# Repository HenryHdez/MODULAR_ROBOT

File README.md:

# **MODULAR ROBOT **
# **PROJECT "PCB"**
Here are all the PCB's for manufacturing the EMERGE modular robot.
# **PROJECT "Optimization_Algorithms.rar" CONTENT**
The content of this project is divided into three sections:
* The first "Module" project must be programmed in all modules of the robotic platform.
* The Second Project "Xbee_Snifer_Teraterm" must be programmed in the accessory card that has an Xbee module only (previously configured) and to perform the data registration you can use the project "Capture_Interface.rar" which is designed in MATLAB and simply begins its registration by pressing the Start button and turn on the robot.
To configure the Xbee module you can follow the following link;
http://xbee.cl/xbee-serie-2-configuracion/
* Finally, there are optimization algorithms, of which you must choose one and program it in the accessory that has the ultrasound sensor only.
# **PROJECT "Robot_Test.rar" CONTENT**
This project is used to test the different peripherals of the robot.
## Test_LED	
This code activates (Frecuency=10Hz) LED lights on each side.
## Test_All_Sensor	
The initialization routine is in charge of turning on the LED located next to each sensor, it will do it 5 times if there is communication with it, otherwise it will only do it once.
Once initialize each sensor, if one of them is obstructed turn on the LED that is next to it.
## Test_Motor	
This program turns on the motor led once it communicates with it, moves it from right to left and vice versa at intervals of 5 seconds.
## Test_Sensor_F1	
All LEDs turn on and off, if there is communication with the face sensor 1.
## Test_Sensor_F2	
All LEDs turn on and off, if there is communication with the face sensor 2.
## Test_Sensor_F3	
All LEDs turn on and off, if there is communication with the face sensor 3.
## Test_Sensor_F4	
All LEDs turn on and off, if there is communication with the face sensor 4.
## Test_CAN_Module_1
Each module sends and receives a data, if the data is accepted, turn on the led of face 2 in each module, otherwise it will not turn on.
## Test_CAN_Module_2	
CAN_Psoc_kit	
Show the information on the CAN bus on an LCD display.

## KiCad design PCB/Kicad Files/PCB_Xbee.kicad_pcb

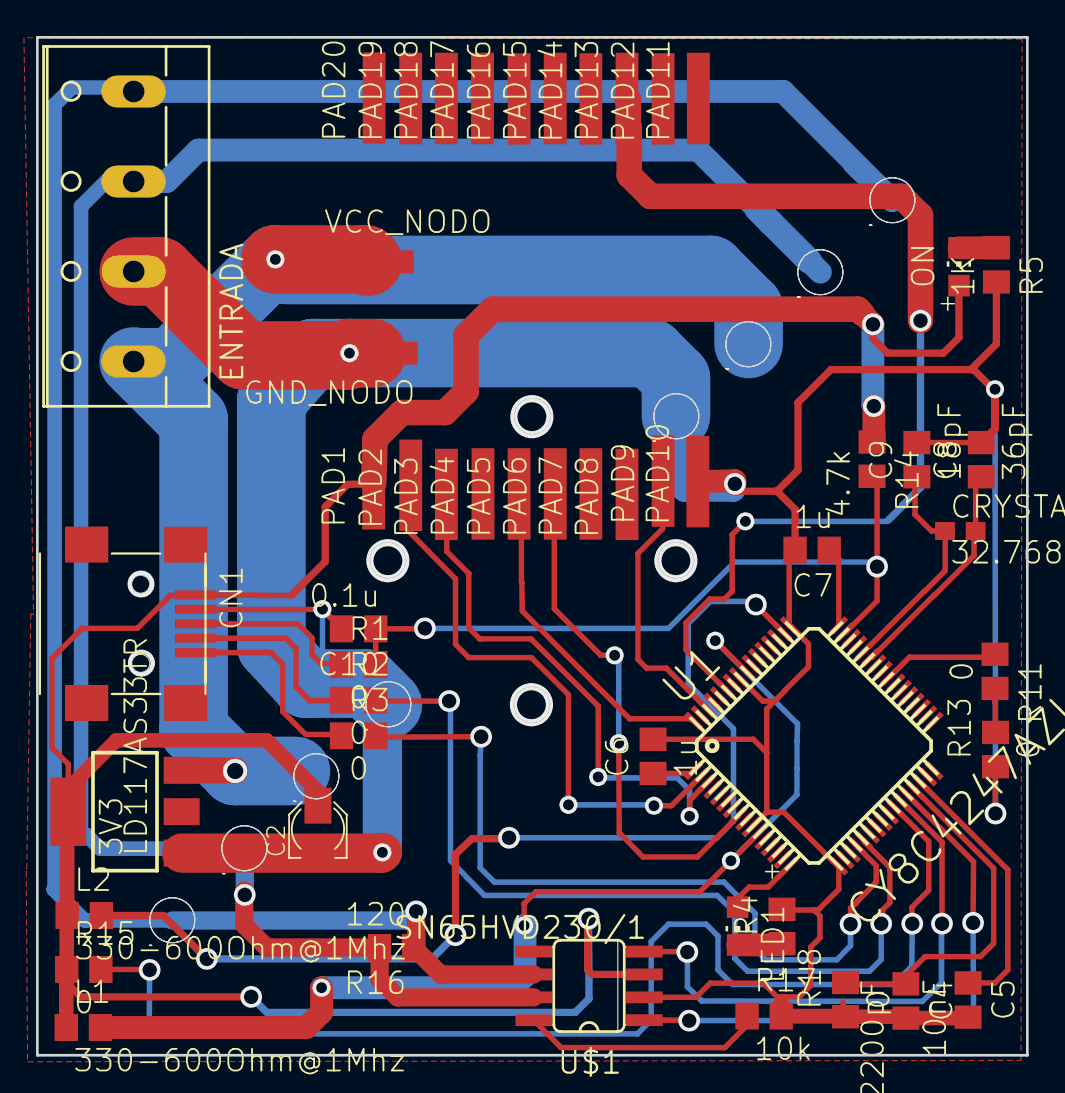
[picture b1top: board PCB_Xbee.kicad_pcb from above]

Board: 2 copper layers, 55.0 x 56.5 mm, 60 parts (0 on the bottom side), 34 nets.

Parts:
3V3: LD117AS33TR; SOT223
C2: PANASONIC_A
C4: 2200pF; C0805
C5: 10nF; C0805
C6, C7: 1u; C0805
C8: 36pF; C0805
C9: 18pF; C0805
C10: 0.1u; C0805
CANH_1_C1, CANH_1_C2: TPB2,54; B2,54
CANL_1_C1, CANL_1_C2: TPB2,54; B2,54
CN1: USB-MINIB
CRYSTAL: 32.768kHz; C0603
ENTRADA: W237-4
GND_1_C1, GND_1_C2: TPB2,54; B2,54
GND_NODO: SMD2,54-5,08
L1, L2: 330-600Ohm@1Mhz; R0805
LED1: CHIP-LED0805
ON: CHIP-LED0805
PAD1, PAD2, PAD3, PAD4, PAD5, PAD6, PAD7, PAD8, PAD9, PAD10, PAD11, PAD12, PAD13, PAD14, PAD15, PAD16, PAD17, PAD18, PAD19, PAD20: SMD2,54-5,08
R1, R2, R3, R11, R13, R15, R18: 0; R0805
R4: R0805
R5: 1K; R0805
R14: 4.7k; R0805
R16: 120; R0805
R17: 10k; R0805
U1: CY8C4247AZI-M485; TQFP64-10X10
U$1: SN65HVD230/1; SO8
VCC_2_C1, VCC_2_C2: TPB2,54; B2,54
VCC_NODO: SMD2,54-5,08

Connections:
3V3: 3V3.4, C2.+, CN1.VBUS, L1.1, L2.1, ON.A, PAD1.1, R14.1, R15.1, U$1.3
CANH: CANH_1_C1.TP, CANH_1_C2.TP, ENTRADA.3, R16.2, U$1.7
CANL: CANL_1_C1.TP, CANL_1_C2.TP, ENTRADA.4, R16.1, U$1.6
CAN_RX: U1.27, U$1.4
CAN_TX: U1.28, U$1.1
CMOD: C4.1, R18.2, U1.29
CTANK: C5.1, U1.30
GND: 3V3.1, C2.-, C4.2, C5.2, C6.2, C7.2, C8.2, C9.2, C10.2, CN1.D-, ENTRADA.2, GND_1_C1.TP, GND_1_C2.TP, GND_NODO.1, PAD10.1, R4.2, R5.2, R13.1, R17.2, R18.1, U1.10, U1.17, U1.49, U1.57, U$1.2
unnamed: CN1.D+, R1.1
unnamed: CN1.ID, R2.1
unnamed: CN1.GND, R3.1
unnamed: R11.2, R13.2
unnamed: LED1.A, U1.16
unnamed: LED1.C, R4.1
unnamed: R17.1, U$1.8
unnamed: ON.C, R5.1
P0_1: R11.1, U1.40
P0_4: C8.1, CRYSTAL.2, U1.43
P0_5: C9.1, CRYSTAL.1, U1.44
RESET_XBEE: PAD5.1, U1.64
RX_STRENGTH: PAD6.1, U1.8
SAR_BY: C6.1, U1.1
SLEEP_CTRL: PAD9.1, U1.62
SLEEP_XBEE: PAD13.1, U1.59
SWDCLK: R2.2, U1.21
SWDIO: R3.2, U1.20
UART_RX: PAD3.1, U1.3
UART_TX: PAD2.1, U1.2
VCCD: C7.1, U1.48
VCC_9-12V: 3V3.3, ENTRADA.1, VCC_2_C1.TP, VCC_2_C2.TP, VCC_NODO.1
VDDA: L1.2, U1.11, U1.56
VDDD: L2.2, U1.50
VDDIO: R15.2, U1.26
XRES: C10.1, R1.2, R14.2, U1.47

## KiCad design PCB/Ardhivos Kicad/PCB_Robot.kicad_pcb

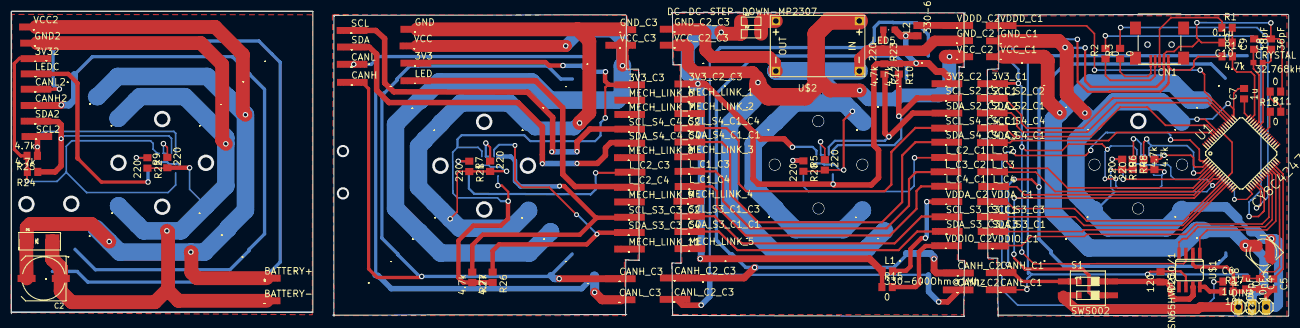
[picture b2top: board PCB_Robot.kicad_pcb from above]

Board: 2 copper layers, 233.5 x 55.8 mm, 205 parts (0 on the bottom side), 86 nets.

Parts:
3V3, 3V3_C1, 3V3_C2, 3V3_C2_C3, 3V3_C3, 3V32: PTR1TP11R; TP11R
BATTERY+: PTR1TP11R; TP11R
BATTERY-: PTR1TP11R; TP11R
C1: UD-5X5,8_NICHICON
C2: UD-8X10_NICHICON
C4: 2200pF; C0805
C5: 10nF; C0805
C6, C7: 1u; C0805
C8: 36pF; C0805
C9: 18pF; C0805
C10: 0.1u; C0805
CANH, CANH2: PTR1TP11R; TP11R
CANH_1_C1, CANH_1_C2, CANH_1_C3, CANH_1_C4, CANH_2_C1, CANH_2_C2, CANH_2_C3, CANH_2_C4, CANH_3_C1, CANH_3_C2, CANH_3_C3, CANH_3_C4, CANH_4_C1, CANH_4_C2, CANH_4_C3, CANH_4_C4: TPB2,54; B2,54
CANH_C1, CANH_C2, CANH_C2_C3, CANH_C3: PTR1TP11R; TP11R
CANL, CANL2: PTR1TP11R; TP11R
CANL_1_C1, CANL_1_C2, CANL_1_C3, CANL_1_C4, CANL_2_C1, CANL_2_C2, CANL_2_C3, CANL_2_C4, CANL_3_C1, CANL_3_C2, CANL_3_C3, CANL_3_C4, CANL_4_C1, CANL_4_C2, CANL_4_C3, CANL_4_C4: TPB2,54; B2,54
CANL_C1, CANL_C2, CANL_C2_C3, CANL_C3: PTR1TP11R; TP11R
CN1: USB-MINIB
CRYSTAL: 32.768kHz; C0603
D1: SMADIODE
D2, D3: SOD-123
DINA: 1X03
GND, GND2: PTR1TP11R; TP11R
GND_1_C1, GND_1_C2, GND_1_C3, GND_1_C4, GND_2_C1, GND_2_C2, GND_2_C3, GND_2_C4, GND_3_C1, GND_3_C2, GND_3_C3, GND_3_C4, GND_4_C1, GND_4_C2, GND_4_C3, GND_4_C4: TPB2,54; B2,54
GND_C1, GND_C2, GND_C2_C3, GND_C3: PTR1TP11R; TP11R
L1, L2: 330-600Ohm@1Mhz; R0805
LED: PTR1TP11R; TP11R
LED1, LED2, LED3, LED4, LED5: CHIPLED_0805
LEDC: PTR1TP11R; TP11R
L_C1_C3, L_C1_C4, L_C2, L_C2_C1, L_C2_C3, L_C2_C4, L_C3, L_C3_C2, L_C4, L_C4_C1: PTR1TP11R; TP11R
MECH_LINK_1, MECH_LINK_2, MECH_LINK_3, MECH_LINK_4, MECH_LINK_5, MECH_LINK_6, MECH_LINK_7, MECH_LINK_8, MECH_LINK_9, MECH_LINK_11: PTR1TP11R; TP11R
R1, R2, R3, R11, R13, R15, R18: 0; R0805
R4, R5, R7, R9, R19, R20, R21, R22, R23: 220; R0805
R6, R8, R10, R12, R14, R24, R25, R26, R27: 4.7k; R0805
R16: 120; R0805
R17: 10k; R0805
S1: SWS002; SMS-002
SCL, SCL2: PTR1TP11R; TP11R
SCL_S2_C2, SCL_S2_C2_C1, SCL_S3_C1_C3, SCL_S3_C3, SCL_S3_C3_C1, SCL_S3_C3_C2, SCL_S4_C1_C4, SCL_S4_C4, SCL_S4_C4_C1, SCL_S4_C4_C2: PTR1TP11R; TP11R
SDA, SDA2: PTR1TP11R; TP11R
SDA_S2_C1, SDA_S2_C2_C2, SDA_S3_C1, SDA_S3_C1_C1, SDA_S3_C3_C3, SDA_S3_C3_C4, SDA_S4_C1, SDA_S4_C1_C1, SDA_S4_C4_C3, SDA_S4_C4_C4: PTR1TP11R; TP11R
U1: CY8C4247AZI-M485; TQFP64-10X10
U2, U3, U4, U5: VCNL4010-GS08; XDCR_VCNL4010-GS08
U$1: SN65HVD230/1; SO8
U$2: DC-DC-STEP-DOWN-MP2307
VCC, VCC2: PTR1TP11R; TP11R
VCC_1_C1, VCC_1_C2, VCC_1_C3, VCC_1_C4, VCC_2_C1, VCC_2_C2, VCC_2_C3, VCC_2_C4, VCC_3_C1, VCC_3_C2, VCC_3_C3, VCC_3_C4, VCC_4_C1, VCC_4_C2, VCC_4_C3, VCC_4_C4: TPB2,54; B2,54
VCC_C1, VCC_C2, VCC_C2_C3, VCC_C3: PTR1TP11R; TP11R
VDDA_C1, VDDA_C2: PTR1TP11R; TP11R
VDDD_C1, VDDD_C2: PTR1TP11R; TP11R
VDDIO_C1, VDDIO_C2: PTR1TP11R; TP11R

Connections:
3V3_C1: 3V3_C1.TP, CN1.VBUS, R6.1, R8.1, R14.1, U2.1, U2.7, U$1.3
3V3_C2: 3V3_C2.TP, 3V3_C2_C3.TP, D2.C, D3.C, L1.1, L2.1, LED5.A, R10.1, R12.1, R15.1, U3.1, U3.7
3V3_C3: 3V3.TP, 3V3_C3.TP, R26.2, R27.2, U4.1, U4.7
3V3_C4: 3V32.TP, R24.2, R25.2, U5.1, U5.7
CANH: CANH_1_C1.TP, CANH_2_C1.TP, CANH_3_C1.TP, CANH_4_C1.TP, CANH_C1.TP, S1.1
CANH_C3: CANH.TP, CANH_1_C3.TP, CANH_2_C3.TP, CANH_3_C3.TP, CANH_4_C3.TP, CANH_C3.TP
CANH_C4: CANH2.TP, CANH_1_C4.TP, CANH_2_C4.TP, CANH_3_C4.TP, CANH_4_C4.TP
CANL: CANL_1_C1.TP, CANL_2_C1.TP, CANL_3_C1.TP, CANL_4_C1.TP, CANL_C1.TP, R16.1, U$1.6
CANL_C3: CANL.TP, CANL_1_C3.TP, CANL_2_C3.TP, CANL_3_C3.TP, CANL_4_C3.TP, CANL_C3.TP
CANL_C4: CANL2.TP, CANL_1_C4.TP, CANL_2_C4.TP, CANL_3_C4.TP, CANL_4_C4.TP
CAN_RX: U1.27, U$1.4
CAN_TX: U1.28, U$1.1
CMOD: C4.1, R18.2, U1.29
CTANK: C5.1, U1.30
DN_1: DINA.1, S1.2
GND3: GND.TP, GND_1_C3.TP, GND_2_C3.TP, GND_3_C3.TP, GND_4_C3.TP, GND_C3.TP, R7.1, R21.2, U4.12, U4.13
GND4: BATTERY-.TP, C2.-, D1.A, GND2.TP, GND_1_C4.TP, GND_2_C4.TP, GND_3_C4.TP, GND_4_C4.TP, R9.1, R22.2, U5.12, U5.13
GND_C1: C1.-, C4.2, C5.2, C6.2, C7.2, C8.2, C9.2, C10.2, CN1.D-, DINA.3, GND_1_C1.TP, GND_2_C1.TP, GND_3_C1.TP, GND_4_C1.TP, GND_C1.TP, R4.2, R13.1, R17.2, R18.1, R19.2, U1.10, U1.17, U1.49, U1.57, U2.12, U2.13, U$1.2
GND_C2: GND_1_C2.TP, GND_2_C2.TP, GND_3_C2.TP, GND_4_C2.TP, GND_C2.TP, GND_C2_C3.TP, R5.1, R20.2, R23.2, U3.12, U3.13, U$2.IN-, U$2.OUT-
LED_S1: LED1.A, U1.4
LED_S2: L_C2.TP, U1.5
LED_S2_C2: LED2.A, L_C2_C1.TP
LED_S3: L_C3.TP, U1.6
LED_S3_C3: LED3.A, L_C2_C3.TP
LED_S4: L_C4.TP, U1.7
LED_S4_C4: LED4.A, LEDC.TP
LED_T_S4: LED.TP, L_C2_C4.TP
MOTOR: S1.3, U1.8, U1.9
unnamed: CN1.D+, R1.1
unnamed: CN1.ID, R2.1
unnamed: CN1.GND, R3.1
unnamed: R11.2, R13.2
unnamed: R16.2, S1.4, U$1.7
unnamed: CANH_1_C2.TP, CANH_2_C2.TP, CANH_3_C2.TP, CANH_4_C2.TP, CANH_C2.TP, CANH_C2_C3.TP
unnamed: R7.2, U4.2, U4.3
unnamed: R17.1, U$1.8
unnamed: SDA_S3_C1_C1.TP, SDA_S3_C3_C3.TP
unnamed: LED1.C, R19.1
unnamed: LED2.C, R20.1
unnamed: LED3.C, R21.1
unnamed: LED4.C, R22.1
unnamed: LED5.C, R23.1
unnamed: L_C1_C4.TP, L_C4_C1.TP
unnamed: R4.1, U2.2, U2.3
unnamed: L_C1_C3.TP, L_C3_C2.TP
unnamed: D2.A, D3.A, U$2.OUT+
unnamed: SCL_S3_C1_C3.TP, SCL_S3_C3_C1.TP
unnamed: SCL_S4_C1_C4.TP, SCL_S4_C4_C1.TP
unnamed: CANL_1_C2.TP, CANL_2_C2.TP, CANL_3_C2.TP, CANL_4_C2.TP, CANL_C2.TP, CANL_C2_C3.TP
unnamed: R5.2, U3.2, U3.3
unnamed: SDA_S4_C1_C1.TP, SDA_S4_C4_C3.TP
unnamed: R9.2, U5.2, U5.3
P0_1: R11.1, U1.40
P0_4: C8.1, CRYSTAL.2, U1.43
P0_5: C9.1, CRYSTAL.1, U1.44
SAR_BY: C6.1, U1.1
SCL_S1: R8.2, U1.2, U2.5
SCL_S2: SCL_S2_C2.TP, U1.51
SCL_S2_U: R10.2, SCL_S2_C2_C1.TP, U3.5
SCL_S3: SCL_S3_C3.TP, U1.12
SCL_S3_U: R27.1, SCL_S3_C3_C2.TP, U4.5
SCL_S4: SCL_S4_C4.TP, U1.58
SCL_S4_U: SCL.TP, SCL_S4_C4_C2.TP
SCL_S4_U_1: R25.1, SCL2.TP, U5.5
SDA_S1: R6.2, U1.3, U2.4
SDA_S2: SDA_S2_C1.TP, U1.52
SDA_S2_U: R12.2, SDA_S2_C2_C2.TP, U3.4
SDA_S3: SDA_S3_C1.TP, U1.13
SDA_S3_U: R26.1, SDA_S3_C3_C4.TP, U4.4
SDA_S4: SDA_S4_C1.TP, U1.59
SDA_S4_U: SDA.TP, SDA_S4_C4_C4.TP
SDA_S4_U_1: R24.1, SDA2.TP, U5.4
SWDCLK: R2.2, U1.21
SWDIO: R3.2, U1.20
VCCC: C1.+, DINA.2, VCC_1_C1.TP, VCC_2_C1.TP, VCC_3_C1.TP, VCC_4_C1.TP, VCC_C1.TP
VCCD: C7.1, U1.48
VCC_C2: U$2.IN+, VCC_1_C2.TP, VCC_2_C2.TP, VCC_3_C2.TP, VCC_4_C2.TP, VCC_C2.TP, VCC_C2_C3.TP
VCC_C3: VCC.TP, VCC_1_C3.TP, VCC_2_C3.TP, VCC_3_C3.TP, VCC_4_C3.TP, VCC_C3.TP
VCC_C4: BATTERY+.TP, C2.+, D1.C, VCC2.TP, VCC_1_C4.TP, VCC_2_C4.TP, VCC_3_C4.TP, VCC_4_C4.TP
VDDA: U1.11, U1.56, VDDA_C1.TP
VDDA2: L1.2, VDDA_C2.TP
VDDD: U1.50, VDDD_C1.TP
VDDD2: L2.2, VDDD_C2.TP
VDDIO: U1.26, VDDIO_C1.TP
VDDIO2: R15.2, VDDIO_C2.TP
XRES: C10.1, R1.2, R14.2, U1.47

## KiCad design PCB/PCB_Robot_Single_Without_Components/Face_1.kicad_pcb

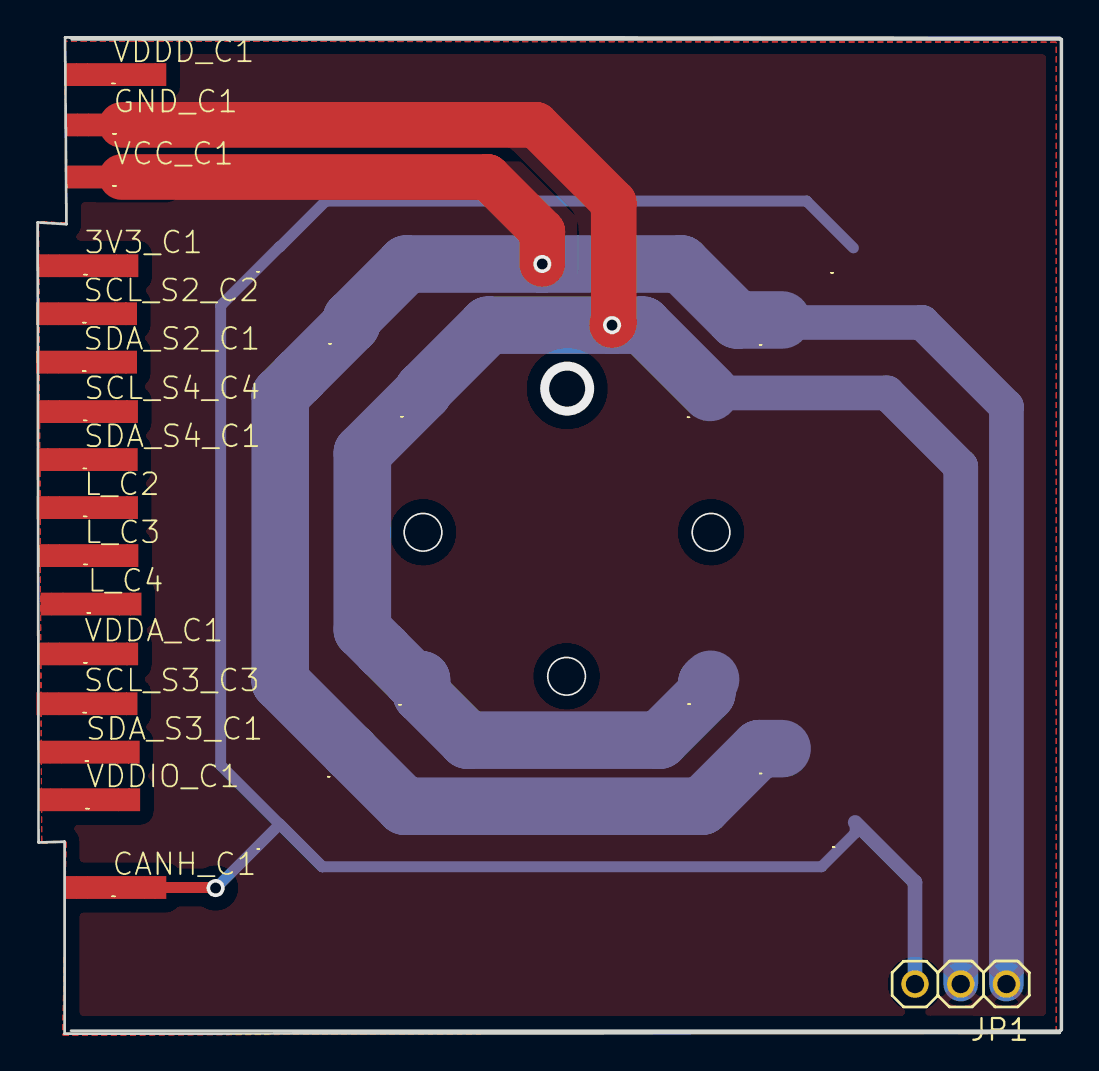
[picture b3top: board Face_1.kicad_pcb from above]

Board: 2 copper layers, 56.9 x 55.4 mm, 29 parts (0 on the bottom side), 3 nets.

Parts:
3V3_C1: PTR1TP11R; TP11R
CANH_1_C1, CANH_2_C1, CANH_3_C1, CANH_4_C1: TPB2,54; B2,54
CANH_C1: PTR1TP11R; TP11R
GND_1_C1, GND_2_C1, GND_3_C1, GND_4_C1: TPB2,54; B2,54
GND_C1: PTR1TP11R; TP11R
JP1: 1X03
L_C2, L_C3, L_C4: PTR1TP11R; TP11R
SCL_S2_C2, SCL_S3_C3, SCL_S4_C4: PTR1TP11R; TP11R
SDA_S2_C1, SDA_S3_C1, SDA_S4_C1: PTR1TP11R; TP11R
VCC_1_C1, VCC_2_C1, VCC_3_C1, VCC_4_C1: TPB2,54; B2,54
VCC_C1: PTR1TP11R; TP11R
VDDA_C1: PTR1TP11R; TP11R
VDDD_C1: PTR1TP11R; TP11R
VDDIO_C1: PTR1TP11R; TP11R

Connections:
CANH: CANH_1_C1.TP, CANH_2_C1.TP, CANH_3_C1.TP, CANH_4_C1.TP, CANH_C1.TP, JP1.3
GND_C1: GND_1_C1.TP, GND_2_C1.TP, GND_3_C1.TP, GND_4_C1.TP, GND_C1.TP, JP1.2
VCCC: JP1.1, VCC_1_C1.TP, VCC_2_C1.TP, VCC_3_C1.TP, VCC_4_C1.TP, VCC_C1.TP

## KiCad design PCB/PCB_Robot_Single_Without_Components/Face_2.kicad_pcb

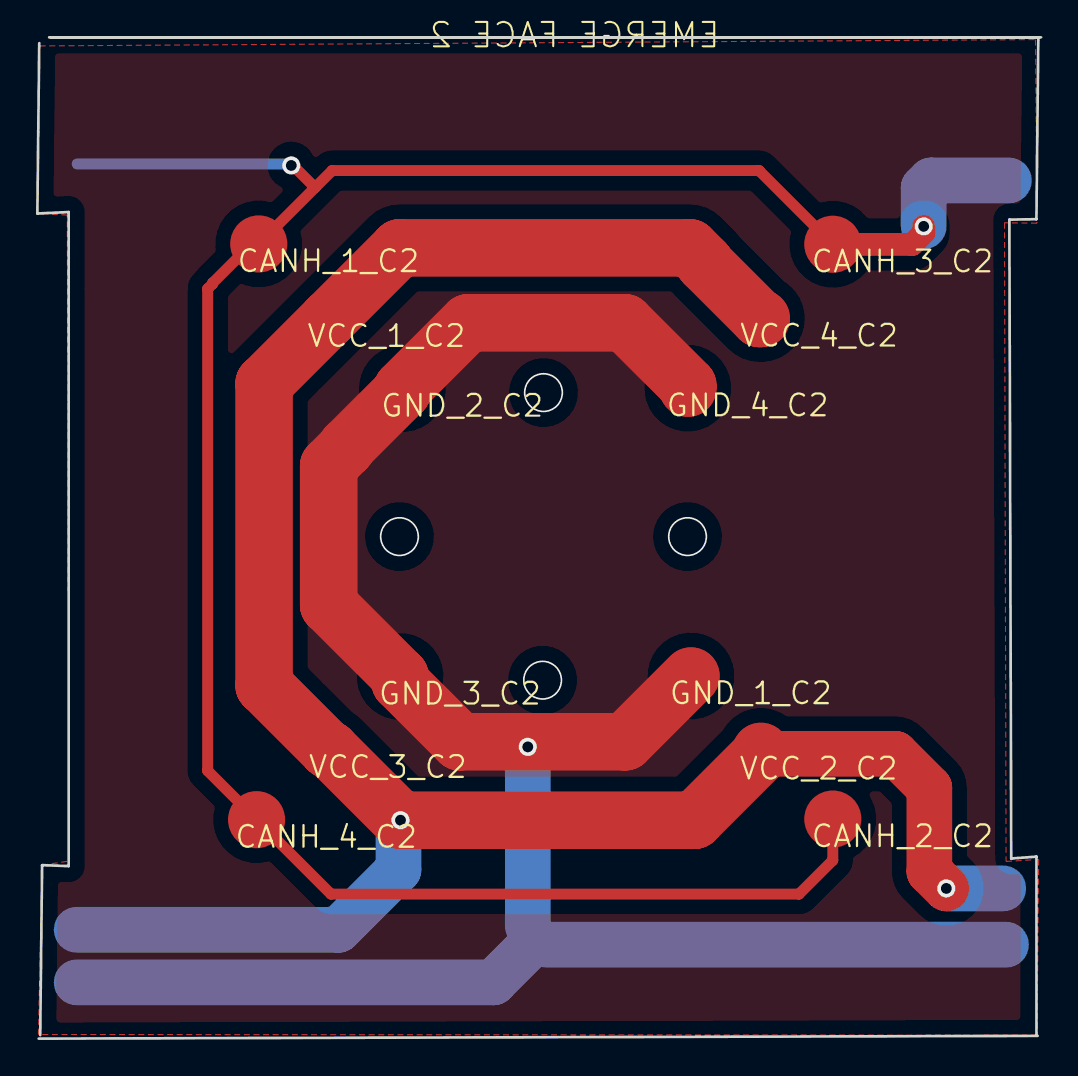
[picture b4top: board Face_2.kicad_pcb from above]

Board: 2 copper layers, 55.8 x 55.6 mm, 43 parts (0 on the bottom side), 3 nets.

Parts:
3V3_C2, 3V3_C2_C3: PTR1TP11R; TP11R
CANH_1_C2, CANH_2_C2, CANH_3_C2, CANH_4_C2: TPB2,54; B2,54
CANH_C2, CANH_C2_C3: PTR1TP11R; TP11R
GND_1_C2, GND_2_C2, GND_3_C2, GND_4_C2: TPB2,54; B2,54
GND_C2, GND_C2_C3: PTR1TP11R; TP11R
L_C1_C3, L_C1_C4, L_C2_C1, L_C3_C2, L_C4_C1: PTR1TP11R; TP11R
MECH_LINK_1, MECH_LINK_2, MECH_LINK_3, MECH_LINK_4, MECH_LINK_5: PTR1TP11R; TP11R
SCL_S2_C2_C1, SCL_S3_C1_C3, SCL_S3_C3_C1, SCL_S4_C1_C4, SCL_S4_C4_C1: PTR1TP11R; TP11R
SDA_S2_C2_C2, SDA_S3_C1_C1, SDA_S3_C3_C3, SDA_S4_C1_C1, SDA_S4_C4_C3: PTR1TP11R; TP11R
VCC_1_C2, VCC_2_C2, VCC_3_C2, VCC_4_C2: TPB2,54; B2,54
VCC_C2, VCC_C2_C3: PTR1TP11R; TP11R
VDDA_C2: PTR1TP11R; TP11R
VDDD_C2: PTR1TP11R; TP11R
VDDIO_C2: PTR1TP11R; TP11R

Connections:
GND_C2: GND_1_C2.TP, GND_2_C2.TP, GND_3_C2.TP, GND_4_C2.TP, GND_C2.TP, GND_C2_C3.TP
unnamed: CANH_1_C2.TP, CANH_2_C2.TP, CANH_3_C2.TP, CANH_4_C2.TP, CANH_C2.TP, CANH_C2_C3.TP
VCC_C2: VCC_1_C2.TP, VCC_2_C2.TP, VCC_3_C2.TP, VCC_4_C2.TP, VCC_C2.TP, VCC_C2_C3.TP

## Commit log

2016-09-27 :neckbeard: Added .gitattributes & .gitignore files
2016-09-27 Init commit
2016-10-19 19 de Octubre de 2016
2016-10-30 30_Oct_2016
    Parcial Changes and Program Probes
2016-11-15 15/11/2016
2017-01-05 5/01/2017
    Add Libraries For modular Robot
2017-01-10 9 de Enero de 2017
    Gerber's Robot and Examples
2017-01-10 10 de Enero de 2017
    Manuales e Indicaciones
2017-01-11 11 de Enero 2017
    Manuals
2017-01-16 15 de Enero de 2017
    Xbee Adapter Agregado
2017-01-16 16 de Enero de 2016
    PCB
2017-02-06 05-Febrero-2017
    CAN Example
2017-04-28 27 Abril 2017
    PCB numero 4
2017-05-02 2-05-2017
    Hoy
2017-05-05 02/May/2017
2017-05-05 05/May
    PCB
2017-05-08 07-May
    PCB_Partido
2017-05-08 8-May
2017-05-08 8_May_2
2017-06-30 29/06/2017
    Gerber
2017-07-17 16/07/2017
2017-08-21 ULTIMA EDICION
2017-08-23 Edicion Diaria
2017-09-25 25-nov
2017-10-18 18_Oct_1017
    Optimization Algoritm OK
2018-01-15 14-ene-18
    At last changes
2018-01-19 18_Ene
    Cambios
2018-01-22 21-Ene
    Cambios
2018-01-22 22/01/2017
    Definitivo
2018-02-05 04/Feb/2018
    Definitivo
2018-11-28 27-Nov
    Ultimas reformas
